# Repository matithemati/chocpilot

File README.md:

# ChocPilot

ChocPilot to przewodowy macropad na własnej płytce ze **STM32F072** i aplikacja na **Windows
i macOS**, w której ustawiasz, co robi każdy element:

- **8 klawiszy Kailh Choc V1** (matryca 2×4) z drukowanymi keycapami,
- kolorowy ekran **[Waveshare 2" IPS LCD 240×320](https://www.tme.eu/pl/details/wsh-17344/wyswietlacze-lcd-graficzne/waveshare/17344/)**
  (ST7789V, SPI; TME WSH-17344) pomiędzy rzędami klawiszy – etykiety albo ikony klawiszy,
  nazwa profilu, nastawy, wygaszacz z animacją i zegarem,
- **2 pokrętła EC11** z przyciskiem i **suwak 45 mm**,
- **12 diod WS2812B** na spodzie (podświetlenie blatu),
- USB-C (USB CDC + HID, bez sterowników).

Firmware jest „cienki”: skanuje klawisze, pokrętła i suwak, rysuje ekran, steruje diodami
i przechowuje kilka ustawień. Całą logikę (gesty, akcje, profile, tryb Klipper) wykonuje
aplikacja. Komunikują się przez USB CDC protokołem JSON Lines ([docs/PROTOCOL.md](docs/PROTOCOL.md)).
Gdy aplikacja nie działa, urządzenie samo wysyła zapisane skróty przez USB HID (tryb awaryjny).

```
firmware/   PlatformIO: chocpilot (STM32F072, STM32duino + TinyUSB), native (testy na PC)
app/        aplikacja Python 3.12+ (PySide6): rdzeń, GUI, symulator, testy, budowanie exe / .app
pcb/        płytka KiCad 10: schemat, PCB, BOM (TME), Gerbery, montaż, mapa pinów
case/       SolidCraft: obudowa, keycapy, gałki, nakładka suwaka, podstawka (STEP / 3MF / STL)
docs/       PROTOCOL.md – protokół urządzenie ↔ aplikacja
```

## Funkcje

- **Gesty**: naciśnięcie, przytrzymanie (próg 500 ms), podwójne naciśnięcie (okno 300 ms).
- **Akcje**: uruchom program (albo przełącz na jego okno; przy kilku oknach kolejne naciśnięcia
  przechodzą między nimi), otwórz plik/folder, adres WWW, skrót klawiszowy (także Win/Cmd,
  F13–F24), wpisz tekst (Unicode), multimedia, głośność systemu i pojedynczego programu
  (Windows), przewijanie, polecenie powłoki, makro, zmiana profilu, warstwa (profil na czas
  trzymania klawisza), tryb Klipper, blokada komputera, wyłączenie ekranu.
- **Profile** z automatycznym przełączaniem według aktywnego programu (np. `obs64.exe` / `OBS`
  → „Stream”), import/eksport do JSON, własny kolor diod dla profilu.
- **Pokrętła i suwak**: każde pokrętło ma akcje dla obrotu w prawo, w lewo i naciśnięcia (te same
  typy akcji co klawisze; głośność i przewijanie mnożą krok przez liczbę zatrzasków). Suwak
  ustawia głośność systemu albo wybranego programu (0–100 %). Domyślnie pokrętło 1 = głośność /
  wycisz, pokrętło 2 = przewijanie / odtwarzaj-pauza.
- **Ekran 320×240**: siatka 2×4 z etykietami albo [ikonami](#ikony-klawiszy) klawiszy, duża
  nazwa profilu, pasek głośności, napis po akcji, znacznik online/offline, tryb testu sprzętu,
  [wygaszacz](#wygaszacz-ekranu) z animacją i godziną. Podgląd w aplikacji rysuje te same piksele.
- **Podświetlenie LED**: stan połączenia, stały kolor, oddychanie, tęcza, wyłączone; błysk diody
  przy naciśniętym klawiszu. Ustawienia zapisane w urządzeniu działają też bez aplikacji.
- **[Tryb Klipper](#tryb-klipper-drukarki-3d)**: sterowanie drukarkami 3D przez Moonraker.
- **Tryb awaryjny HID**: po 3 s bez sygnału z aplikacji klawisze wysyłają skróty wyliczone
  z profilu (akcje „skrót” i „multimedia”), pokrętło 1 zmienia głośność; domyślnie dolny rząd:
  ciszej, głośniej, odtwarzaj/pauza, wycisz.

## Sprzęt

Wszystko o płytce jest w [pcb/README.md](pcb/README.md):

- lista części z numerami TME: [pcb/bom/BOM.md](pcb/bom/BOM.md) (wszystko poza przełącznikami
  Kailh jest w TME, łącznie z ekranem),
- kolejność lutowania i uruchomienie: [pcb/docs/ASSEMBLY.md](pcb/docs/ASSEMBLY.md),
- mapa pinów MCU i złączy: [pcb/docs/PINOUT.md](pcb/docs/PINOUT.md),
- decyzje projektowe, zasilanie, sygnały: [pcb/docs/DESIGN_NOTES.md](pcb/docs/DESIGN_NOTES.md),
- Gerbery do zamówienia płytek: `pcb/fab/gerbers/` (2 warstwy, 1,6 mm – standard JLCPCB / PCBWay).

Obudowa, keycapy, gałki pokręteł, nakładka suwaka i podstawka pod kątem 20°:
[case/README.md](case/README.md) (gotowe pliki STL / 3MF do druku).

Ekran Waveshare 2" przykręca się 4 wkrętami M2 do obudowy i łączy dołączonym kablem PH2.0
ze złączem J2 płytki (1:1, zasilanie 3,3 V).

## Firmware

Wymagania: [PlatformIO](https://platformio.org/) (VS Code + rozszerzenie albo `pip install platformio`).

```bash
cd firmware
pio run
```

- **Rdzeń**: Arduino STM32duino (platforma `ststm32`, płytka `boards/chocpilot.json` = wariant
  generic F072CB), zegar 48 MHz z HSI48 bez kwarcu, dostrajany przez CRS do ramek USB.
- **USB**: [TinyUSB](https://github.com/hathach/tinyusb) 0.18 – urządzenie złożone CDC + HID
  (klawiatura i consumer control), nazwa „ChocPilot”, VID:PID **1209:0001** (pid.codes).
  Aplikacja znajduje port po nazwie, zapasowo po tej parze.
- **Ekran** (`src/display_tft.cpp`, `src/st7789.cpp`): SPI1 12 MHz, tryb 3, bez bufora ramki –
  rysowane są tylko zmienione fragmenty, a po serii komend (np. ikony przy zmianie profilu)
  ekran odświeża się raz, gdy zmiany ustaną. Jasność = PWM podświetlenia, `flip` = obrót o 180°.
  Krój 5×7 ASCII w kilku skalach – polskie litery tracą ogonki (ą → a).
- **Matryca** 2×4 COL2ROW z mapą klawiszy z płytki (`src/boards/board.h`).
- **Pokrętła i suwak** (`src/controls.cpp`): TIM2/TIM3 w trybie enkodera, suwak przez ADC
  z filtrem i histerezą. **Offline** pokrętło 1 zmienia głośność, jego przycisk wycisza.
- **LED** (`src/leds.cpp`, SPI2 3 MHz; efekty `lib/chocpilotcore/src/led_effects.cpp`): jasność
  ograniczona do ok. 1/3 (prąd z USB), przy wygaszaczu wyłączone, w trybie testu kolejno R / G / B / biały.
- **Wygaszacz** (`src/saver.cpp`): animacje z `app/chocpilot/core/savers.py` (jedno źródło dla
  firmware i podglądu) – `python firmware/tools/gen_savers.py` generuje z nich `src/saver_data.h`.
- **Ikony klawiszy** (`src/icons.cpp`): 32×32 px, 16 kolorów, tylko w RAM (aplikacja wysyła je
  po połączeniu).
- **Ustawienia** w emulacji EEPROM rdzenia (ostatnia strona flash) jako blok binarny z CRC
  i numerem wersji – nowsze wersje firmware czytają zapisy starszych.
- **Zużycie** (2026-11, `pio run`): **flash 56 500 B / 128 KB (43 %)**, **RAM 11 228 B / 16 KB (69 %)**.

### Wgrywanie (bootloader DFU w ROM)

Windows:

```powershell
cd firmware
.\flash.ps1
```

Skrypt kompiluje firmware, przełącza działającą płytkę w bootloader (komenda `reboot`) i wgrywa
program przez dfu-util. Opcje: `-BuildOnly` (tylko kompilacja), `-CloseApp` (najpierw zamyka
aplikację ChocPilot, która trzyma port). Bez skryptu (Windows i macOS):

1. Wejście do bootloadera: w aplikacji **Urządzenie → Tryb wgrywania firmware** albo przyciski
   na spodzie płytki (dostęp przez otwory w dnie): trzymaj **BOOT0**, naciśnij i puść **RESET**,
   puść BOOT0. System widzi wtedy „STM32 BOOTLOADER” (0483:DF11).
2. `pio run -t upload` – po wgraniu płytka sama uruchamia program.

Windows za pierwszym razem: przypisz urządzeniu „STM32 BOOTLOADER” sterownik **WinUSB**
programem [Zadig](https://zadig.akeo.ie/) (albo wgraj `.pio\build\chocpilot\firmware.bin` od
adresu 0x08000000 w STM32CubeProgrammer). macOS nie potrzebuje sterownika.

### Testy firmware (na PC)

Parser protokołu, debounce, kody HID, zapis konfiguracji i efekty LED mają testy jednostkowe
w środowisku `native`. Potrzebny jest kompilator gcc/g++ w PATH (Windows: MinGW-w64 –
`pio pkg install -g -t platformio/toolchain-gccmingw32` i dodanie
`%USERPROFILE%\.platformio\packages\toolchain-gccmingw32\bin` do PATH; macOS: Xcode Command Line Tools).

```bash
pio test -e native
```

## Aplikacja

Wymagania: Windows 10/11 albo macOS 12+, Python **3.12+** (sprawdzone na 3.14).

Windows:

```powershell
cd app
python -m venv .venv
.venv\Scripts\python -m pip install -e ".[dev]"
.venv\Scripts\python -m chocpilot
```

macOS:

```bash
cd app
python3 -m venv .venv
.venv/bin/python -m pip install -e ".[dev]"
.venv/bin/python -m chocpilot
```

| Opcja | Działanie |
|---|---|
| `--minimized` | start w zasobniku (macOS: pasek menu) |
| `--config PLIK` | inny plik konfiguracji |
| `--verbose` | dziennik na konsoli |
| `--simulate` | tryb deweloperski: okno symulatora płytki (klawisze, pokrętła, suwak, LED, podgląd LCD) zamiast urządzenia |
| `--version` | wersja aplikacji |

Konfiguracja i dziennik:

| System | Katalog |
|---|---|
| Windows | `%APPDATA%\ChocPilot` |
| macOS | `~/Library/Application Support/ChocPilot` |

`config.json` (zapis atomowy, poprzednia wersja w `config.json.bak`), `chocpilot.log`
(rotacja 3 × 512 KB), `icons/` (własne ikony). Uszkodzony plik konfiguracji jest odkładany
jako `config.broken.json`, a aplikacja wczytuje kopię zapasową. Nieobsłużone błędy trafiają do
dziennika z pełnym śladem i pokazują jedno okno z informacją – aplikacja działa dalej.

Obsługa:

- Lista profili po lewej (dwuklik = aktywuj). Kliknij klawisz, pokrętło albo suwak na podglądzie,
  aby edytować; przyciski **Testuj** wykonują akcję od razu. Fizyczne naciśnięcia podświetlają
  elementy podglądu.
- **Plik → Ustawienia**: port (auto/ręczny), jasność, wygaszacz i jego animacja, tryb ekranu,
  obrót, podświetlenie LED (podgląd na żywo), progi gestów, debounce, skróty trybu awaryjnego,
  autostart, start zminimalizowany, motyw, język (PL/EN).
- Zamknięcie okna chowa aplikację do zasobnika (kolor ikony = stan połączenia). Z zasobnika:
  zmiana profilu, **Wstrzymaj akcje**, wyjście. Uruchamia się tylko jedna instancja.

### macOS – uprawnienia i ograniczenia

- **Dostępność** (Ustawienia systemowe → Prywatność i ochrona → Dostępność): wymagana do skrótów,
  wpisywania tekstu, przewijania, blokady ekranu i przełączania okien. Przy pierwszym starcie
  macOS sam pokazuje prośbę, a aplikacja wyjaśnia, co włączyć; po włączeniu uruchom ją ponownie.
- **Automatyzacja**: przy pierwszym poleceniu powłoki uruchamianym w widocznym oknie macOS pyta
  o zgodę na sterowanie Terminalem (AppleScript) – zezwól.
- Głośność **pojedynczego programu** nie jest dostępna (macOS nie ma do tego publicznego API);
  głośność systemu działa.
- Autostart = LaunchAgent `~/Library/LaunchAgents/com.chocpilot.app.plist` (włączany w Ustawieniach).

### Testy i jakość

```bash
cd app
.venv/Scripts/python -m pytest          # macOS: .venv/bin/python
.venv/Scripts/python -m ruff check chocpilot tests
.venv/Scripts/python -m ruff format --check chocpilot tests
.venv/Scripts/python -m mypy chocpilot
```

Testy nie wymagają urządzenia (atrapy portu szeregowego, platformy i symulator). Testy GUI
działają w trybie `offscreen` (pytest-qt).

### Budowanie – Windows (ChocPilot.exe)

```powershell
cd app
.\build_exe.ps1
```

Skrypt instaluje zależności, generuje ikony (`scripts/make_icon.py`) i uruchamia PyInstaller
(`chocpilot.spec`): jeden plik bez konsoli, z ikoną i metadanymi wersji (Właściwości pliku).
Wynik: `app\dist\ChocPilot.exe`. Działającą kopię z `dist` skrypt zamyka przed budowaniem
i uruchamia ponownie (`-NoRestart` – bez ponownego uruchomienia).

### Budowanie – macOS (ChocPilot.app)

```bash
cd app
./build_macos.sh
```

Skrypt (na Macu, z Pythonem 3.12+ z python.org albo Homebrew i Xcode Command Line Tools)
tworzy `.venv`, uruchamia testy, generuje ikonę `.icns`, buduje **`dist/ChocPilot.app`**
(PyInstaller, architektura Pythona – na Apple Silicon `arm64`), podpisuje ją ad-hoc i pakuje
do **`dist/ChocPilot-<wersja>-macOS-<arch>.dmg`** (przeciągnij do Aplikacji). Opcje:
`--skip-tests`, `--no-dmg`.

- Pierwsze uruchomienie aplikacji podpisanej ad-hoc: Finder → prawy klik → **Otwórz** (albo
  `xattr -dr com.apple.quarantine /Applications/ChocPilot.app`), bo Gatekeeper nie zna autora.
- Do dystrybucji innym osobom: `CODESIGN_IDENTITY="Developer ID Application: …" ./build_macos.sh`
  podpisuje certyfikatem Apple (hardened runtime); potem notaryzacja:
  `xcrun notarytool submit dist/ChocPilot-*.dmg --keychain-profile <profil> --wait`
  i `xcrun stapler staple dist/ChocPilot-*.dmg`.
- Po każdej przebudowie podpisanej ad-hoc macOS może zapomnieć uprawnienie Dostępność – wyłącz
  i włącz ChocPilot na liście (albo usuń i dodaj ponownie).

### Wersje

Jedno źródło wersji aplikacji: `app/chocpilot/__init__.py` (`__version__`) – używają go pakiet
Pythona, okno „O programie”, metadane exe i `Info.plist`. Wersja firmware: `CHOCPILOT_FW_VERSION`
w `firmware/platformio.ini`; aplikacja pokazuje ją na pasku stanu.

### Architektura aplikacji

```
chocpilot/core/protocol.py    kodowanie/dekodowanie JSON Lines, walidacja, transliteracja (krój ASCII)
chocpilot/core/transport.py   interfejs + port szeregowy (wątek, wykrywanie, ponowne łączenie)
chocpilot/core/simulator.py   symulator urządzenia (ta sama logika co firmware) + transport w procesie
chocpilot/core/gestures.py    tap / hold / double_tap (czysta logika, czas z zewnątrz)
chocpilot/core/actions/       rejestr typów akcji, wbudowane akcje, wykonawca (pula wątków)
chocpilot/core/config.py      modele pydantic, migracje schema_version, zapis atomowy, import/eksport
chocpilot/core/profiles.py    aktywny profil, warstwy, automatyczne przełączanie
chocpilot/core/engine.py      kontroler: zdarzenia → gesty → akcje; profil → ekran, ikony, LED, skróty HID
chocpilot/core/klipper.py     tryb Klipper (moonraker.py – klient HTTP Moonrakera)
chocpilot/core/leds.py        efekty LED (jak firmware – podgląd), savers.py – animacje wygaszacza
chocpilot/platform/           kod zależny od systemu: windows.py, macos.py (base.py = interfejs)
chocpilot/gui/                PySide6: okno główne, edytory, ustawienia, zasobnik, symulator
chocpilot/gui/lcd.py          podgląd ekranu LCD 320×240 – ten sam krój i układ co firmware
chocpilot/gui/icon_*.py       biblioteka i wybór ikon klawiszy
```

Nowy typ akcji: klasa dziedzicząca po `ActionBase` z polem `type: Literal["nazwa"]`, metodą
`run(ctx)` i dekoratorem `@register_action("nazwa", "Etykieta")`. Formularz w GUI tworzy się
automatycznie z pól modelu.

## Ikony klawiszy

Każdy klawisz może mieć na ekranie ikonę zamiast etykiety: edytor klawisza → **Ikona na
ekranie** → *Wybierz ikonę…*. Okno wyboru ma wyszukiwarkę i kategorie:

- **wbudowane** – ok. 120 ikon liniowych (multimedia, edycja, programy, system, streaming, druk 3D,
  symbole), zdefiniowane w `app/chocpilot/gui/icon_set.py`; nowa ikona = jeden wiersz SVG,
- **emoji** – wszystkie emoji czcionki systemu (Windows: Segoe UI Emoji, macOS: Apple Color
  Emoji), wyszukiwane po angielskiej nazwie Unicode,
- **własne** – pliki PNG / SVG / JPG z folderu `icons` w katalogu konfiguracji (przycisk *Folder
  własnych ikon*, potem *Odśwież*).

Aplikacja zamienia ikonę na 32 × 32 px w 16 kolorach na tle kafelka i wysyła ją do urządzenia
(komenda `icon`), które rysuje ją w skali 2. Przy zmianie profilu ikony idą przed siatką, więc
nowy ekran pojawia się od razu z kompletem ikon. Etykieta zostaje – pokazuje się w podglądzie
po naciśnięciu i po restarcie płytki bez aplikacji.

## Wygaszacz ekranu

Po czasie `screensaver_s` (Ustawienia → Urządzenie) ekran gaśnie albo pokazuje animację –
po trawie skacze królik albo kłusuje corgi, a u góry na środku jest godzina HH:MM (czas podaje
aplikacja, płytka liczy dalej sama). Wybór: **Ustawienia → Urządzenie → Animacja wygaszacza**.
Dowolny klawisz / pokrętło budzi ekran, diody LED w tym czasie są zgaszone. Nowa animacja =
wpis w `SAVERS` (`app/chocpilot/core/savers.py`, ramki jako tekst) + `firmware/tools/gen_savers.py`.

## Tryb Klipper (drukarki 3D)

ChocPilot może sterować drukarkami 3D z [Klipperem](https://www.klipper3d.org/) przez API
[Moonrakera](https://moonraker.readthedocs.io/) (to samo, którego używają Mainsail i Fluidd).
Konfiguracja: strona **Klipper** w aplikacji.

- **Drukarki:** nazwa, adres Moonrakera (np. `http://voron.local` albo `192.168.1.20:7125`),
  opcjonalny klucz API; przycisk *Testuj połączenie* pokazuje stan drukarki.
- **Włączanie trybu:** przytrzymaj przycisk pokrętła E2 (domyślnie 0,8 s; do wyboru E1 albo tylko
  akcja). Krótkie naciśnięcie tego pokrętła działa jak zwykle (wykonuje się po puszczeniu).
  Akcję **Tryb Klipper** (włącz / wyłącz / przełącz) można też przypisać do dowolnego klawisza.
- **W trybie Klipper:**
  - klawisze K1–K8 – polecenia z ustawień (każde z ikoną): G-code / makro, pauza / wznowienie,
    anuluj wydruk, awaryjne zatrzymanie, restart firmware, następna drukarka, wyjście. Domyślnie:
    Home, Pauza, PLA (stół 60 °C, dysza 200 °C), Stygnij, Silniki, Anuluj (przytrzymanie),
    Drukarka, STOP (przytrzymanie);
  - pokrętło E1 – ruch osi (naciśnięcie: X → Y → Z, krok i prędkość w ustawieniach; wymaga
    bazowania osi); w trakcie wydruku – Z offset w locie (`SET_GCODE_OFFSET Z_ADJUST`);
  - pokrętło E2 – temperatura dyszy / stołu, prędkość (M220), przepływ (M221), wentylator;
    naciśnięcie zmienia parametr;
  - suwak – wentylator chłodzenia albo prędkość wydruku 50–150 %;
  - ekran – w tytule nazwa drukarki, stan (postęp wydruku) i temperatury, w siatce ikony
    poleceń; nastawy pokazują się na chwilę na ekranie.
- Szybkie kręcenie pokrętłem wysyła tylko najnowszą nastawę (bez kolejki starych poleceń).
  Klucz API jest zapisywany w pliku konfiguracji aplikacji.

## Rozwiązywanie problemów

| Objaw | Co sprawdzić |
|---|---|
| Aplikacja „szuka ChocPilot…” | Kabel z transmisją danych (nie tylko ładowanie). Zamknij monitor portu PlatformIO (port może być zajęty). W Ustawieniach wybierz port ręcznie (Windows: `COMx`, macOS: `/dev/cu.usbmodem…`). Dziennik pokazuje próby. |
| Płytka nie pojawia się w systemie | Sprawdź **+5V** i **+3V3** (pcb/docs/ASSEMBLY.md, test 1) i lut USB-C. Płytka bez firmware zgłasza się tylko jako „STM32 BOOTLOADER” – wgraj firmware. |
| `flash.ps1` / `pio run -t upload`: brak urządzenia DFU | Windows: sterownik WinUSB dla „STM32 BOOTLOADER” (Zadig). Wejdź do bootloadera ręcznie: BOOT0 + RESET. |
| Pusty / biały ekran | Kabel PH2.0 do J2 (VCC na pin 1, kolejność 1:1), lut J2. W trybie testu (K1 + K4 przez 3 s po podłączeniu) ekran pokazuje stan klawiszy. |
| Obraz do góry nogami | Ustawienia → Urządzenie → **Obróć ekran o 180°**. |
| Polskie litery bez ogonków | To nie błąd: krój ekranu ma tylko ASCII. |
| Kilka klawiszy reaguje naraz | Odwrócona dioda albo brak diody; sprawdź w trybie testu sprzętu. |
| Klawisz „drga” | Zwiększ debounce (Ustawienia → Urządzenie). |
| Pokrętło działa odwrotnie | Kierunek w firmware: `kEncoderDir` w `firmware/src/boards/board.h`. |
| Przełączanie na okno programu nie działa | Windows czasem blokuje przejęcie fokusu (program i tak jest uruchamiany, gdy nie ma okna); macOS – uprawnienie Dostępność. |
| Skróty i tekst nic nie robią (macOS) | Uprawnienie **Dostępność** dla ChocPilot (po przebudowie aplikacji wyłącz i włącz je ponownie). |
| Głośność programu „nie gra” | Windows: program musi mieć aktywną sesję audio (widoczną w mikserze głośności). macOS: funkcja niedostępna. |
| SmartScreen / antywirus ostrzega o ChocPilot.exe | Plik nie jest podpisany; pynput (symulacja klawiatury) bywa oznaczany heurystycznie. Można uruchamiać z Pythona. |
| Akcje wykonują się podwójnie | Nie powinno: gdy aplikacja jest połączona, HID urządzenia jest wyłączony. Sprawdź, czy nie działają dwie kopie aplikacji (np. zbudowana i z Pythona). |
| Coś innego | Zakładka **Dziennik** w aplikacji albo `chocpilot.log` w katalogu konfiguracji. |

## Licencja

MIT.

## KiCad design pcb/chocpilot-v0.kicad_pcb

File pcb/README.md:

# ChocPilot – płytka (KiCad 10)

Sprzęt ChocPilot (rewizja płytki **v0** – nazwa plików KiCad): 8 klawiszy Kailh Choc V1 lutowanych w płytkę (2 rzędy po 4, matryca
z diodą przy każdym klawiszu),
kolorowy ekran [Waveshare 2" IPS LCD 240×320](https://www.tme.eu/pl/details/wsh-17344/wyswietlacze-lcd-graficzne/waveshare/17344/)
(TME WSH-17344, ST7789V, SPI; przykręcony do obudowy) pomiędzy nimi, 2 enkodery EC11 po lewej, suwak 45 mm po prawej,
12 diod WS2812B na spodzie (podświetlenie blatu) i własny mikrokontroler STM32F072 z USB-C.
Płytka 114 × 93 mm, 2 warstwy, wszystko poza elementami istniejącymi tylko w THT – SMD
w obudowach do ręcznego lutowania (0805, SOT-23, LQFP-48).

| Plik | Zawartość |
|---|---|
| `chocpilot-v0.kicad_pro/.kicad_sch/.kicad_pcb` | projekt KiCad 10 (schemat A3, płytka z trasami i wylewkami GND) |
| `chocpilot.pretty/` | footprinty własne: Kailh Choc V1/V2 (THT), suwak ALPS RS45111 |
| [bom/BOM.md](bom/BOM.md), [bom/chocpilot-v0-bom.csv](bom/chocpilot-v0-bom.csv) | lista części z numerami TME / Amazon |
| [docs/PINOUT.md](docs/PINOUT.md) | mapa pinów MCU, złącza, kolejność LED |
| [docs/ASSEMBLY.md](docs/ASSEMBLY.md) | kolejność lutowania i uruchomienie |
| [docs/DESIGN_NOTES.md](docs/DESIGN_NOTES.md) | decyzje projektowe, zasilanie, sygnały, rzeczy do sprawdzenia przed zamówieniem |
| `img/` | podgląd: `schematic.pdf/.png`, `pcb_top/bottom.png` (warstwy), `render_top/bottom.png` (3D) |
| `fab/gerbers/` | Gerbery + wiercenia (Excellon) do zamówienia płytek – spakuj zawartość do ZIP albo `tools/export_fab.sh` |
| `production/` | pliki montażu SMT (BOM, pozycje elementów, netlista IPC) z wtyczki Fabrication Toolkit |
| `tools/` | generatory – patrz niżej |

## Dlaczego STM32F072CBT6, a nie RP2040

- **Obudowa.** RP2040 istnieje tylko jako QFN-56 0,4 mm z padem termicznym pod spodem – bez
  gorącego powietrza / pieca praktycznie nie do przylutowania kolbą. STM32F072CBT6 to
  **LQFP-48 0,5 mm z wyprowadzeniami na zewnątrz**: lutuje się zwykłą kolbą metodą „drag”
  z topnikiem, a mostki widać i łatwo zebrać plecionką.
- **Mniej części.** F072 ma USB FS **bez kwarcu** (HSI48 synchronizowany przez CRS z ramkami
  USB), pamięć programu w środku (128 KB) i **bootloader USB DFU w ROM** (BOOT0 + RESET).
  RP2040 wymaga zewnętrznego flasha QSPI (SOIC-8 lub USON), kwarcu 12 MHz i dodatkowego
  odsprzęgania wewnętrznego regulatora 1,1 V.
- **Wystarczająca wydajność.** F072 ma 128 KB flash / 16 KB RAM (firmware zajmuje ok. 43 % /
  69 %), sprzętowe SPI, ADC 12-bit, timery z trybem enkodera (TIM2, TIM3) i SPI do sterowania
  WS2812.
- **Dostępność.** STM32F072CBT6 jest w TME, wspierany przez STM32duino (PlatformIO `ststm32`)
  i QMK.

Kwarc 8 MHz (Y1) jest na płytce jako **opcja** – USB go nie potrzebuje; daje dokładniejszy zegar,
jeśli kiedyś będzie potrzebny (można nie lutować Y1, C13, C14).

## Weryfikacja (KiCad 10.0.7, `kicad-cli`)

- **ERC:** 0 błędów, 0 ostrzeżeń.
- **DRC** (`--severity-all --schematic-parity`, także z `--refill-zones`): 0 naruszeń,
  0 niepołączonych, 0 rozbieżności ze schematem.
- Reguły: odstęp miedź–miedź 0,2 mm, ścieżki 0,25 mm (sygnały) / 0,3 mm (+3V3, GND) /
  0,6 mm (VBUS, +5V), przelotki 0,6/0,3 mm, krawędź 0,3 mm (trasowane z 0,5 mm), otwór–miedź
  0,15 mm (kołki ustalające USB-C mają 0,19 mm do padów GND w bibliotecznym footprincie).
  Mieści się w standardzie tanich fabryk (JLCPCB, PCBWay: 2 warstwy, 1,6 mm, 1 oz).

Do zrobienia przed zamówieniem płytek – patrz [DESIGN_NOTES.md](docs/DESIGN_NOTES.md#do-sprawdzenia-przed-zamowieniem):
wydruk 1:1 i przymiarka footprintu Choc, mocowanie ekranu LCD w obudowie i długość jego kabla do J2, przymiarka footprintu suwaka ALPS.

## Generowanie

Schemat, płytka i BOM powstają ze skryptów w `tools/` (dane: [`tools/design.py`](tools/design.py)).
Ręczne poprawki w KiCad są możliwe, ale kolejne generowanie je nadpisze – zmieniaj `design.py`.

```bash
cd pcb
python3 tools/gen_pro.py        # reguły DRC i klasy sieci
python3 tools/gen_sch.py        # schemat
/Applications/KiCad/KiCad.app/Contents/Frameworks/Python.framework/Versions/Current/bin/python3 tools/gen_pcb.py
python3 tools/gen_bom.py        # BOM.md + CSV
tools/render.sh img             # podgląd PNG
tools/export_fab.sh             # Gerbery
```

Windows (KiCad 10 w `C:\Program Files\KiCad\10.0`, inna ścieżka – zmienna `KICAD_ROOT`;
ścieżki instalacji są w [`tools/kicad_env.py`](tools/kicad_env.py)):

```bash
python tools/gen_sch.py
"/c/Program Files/KiCad/10.0/bin/python.exe" tools/gen_pcb.py
python tools/gen_bom.py
```

`gen_pcb.py` używa Pythona dołączonego do KiCad (moduł `pcbnew`), eksportuje netlistę ze
schematu przez `kicad-cli` i trasuje płytkę własnym routerem [`tools/router.py`](tools/router.py)
(A* na siatce 0,25 mm, 2 warstwy; ok. 1 min). `--reuse` używa zapisanych tras z
`tools/build/`. Na macOS `kicad-cli` uruchamiany z piaskownicy potrafi zawisnąć przy starcie –
wtedy trzeba go uruchomić poza nią.

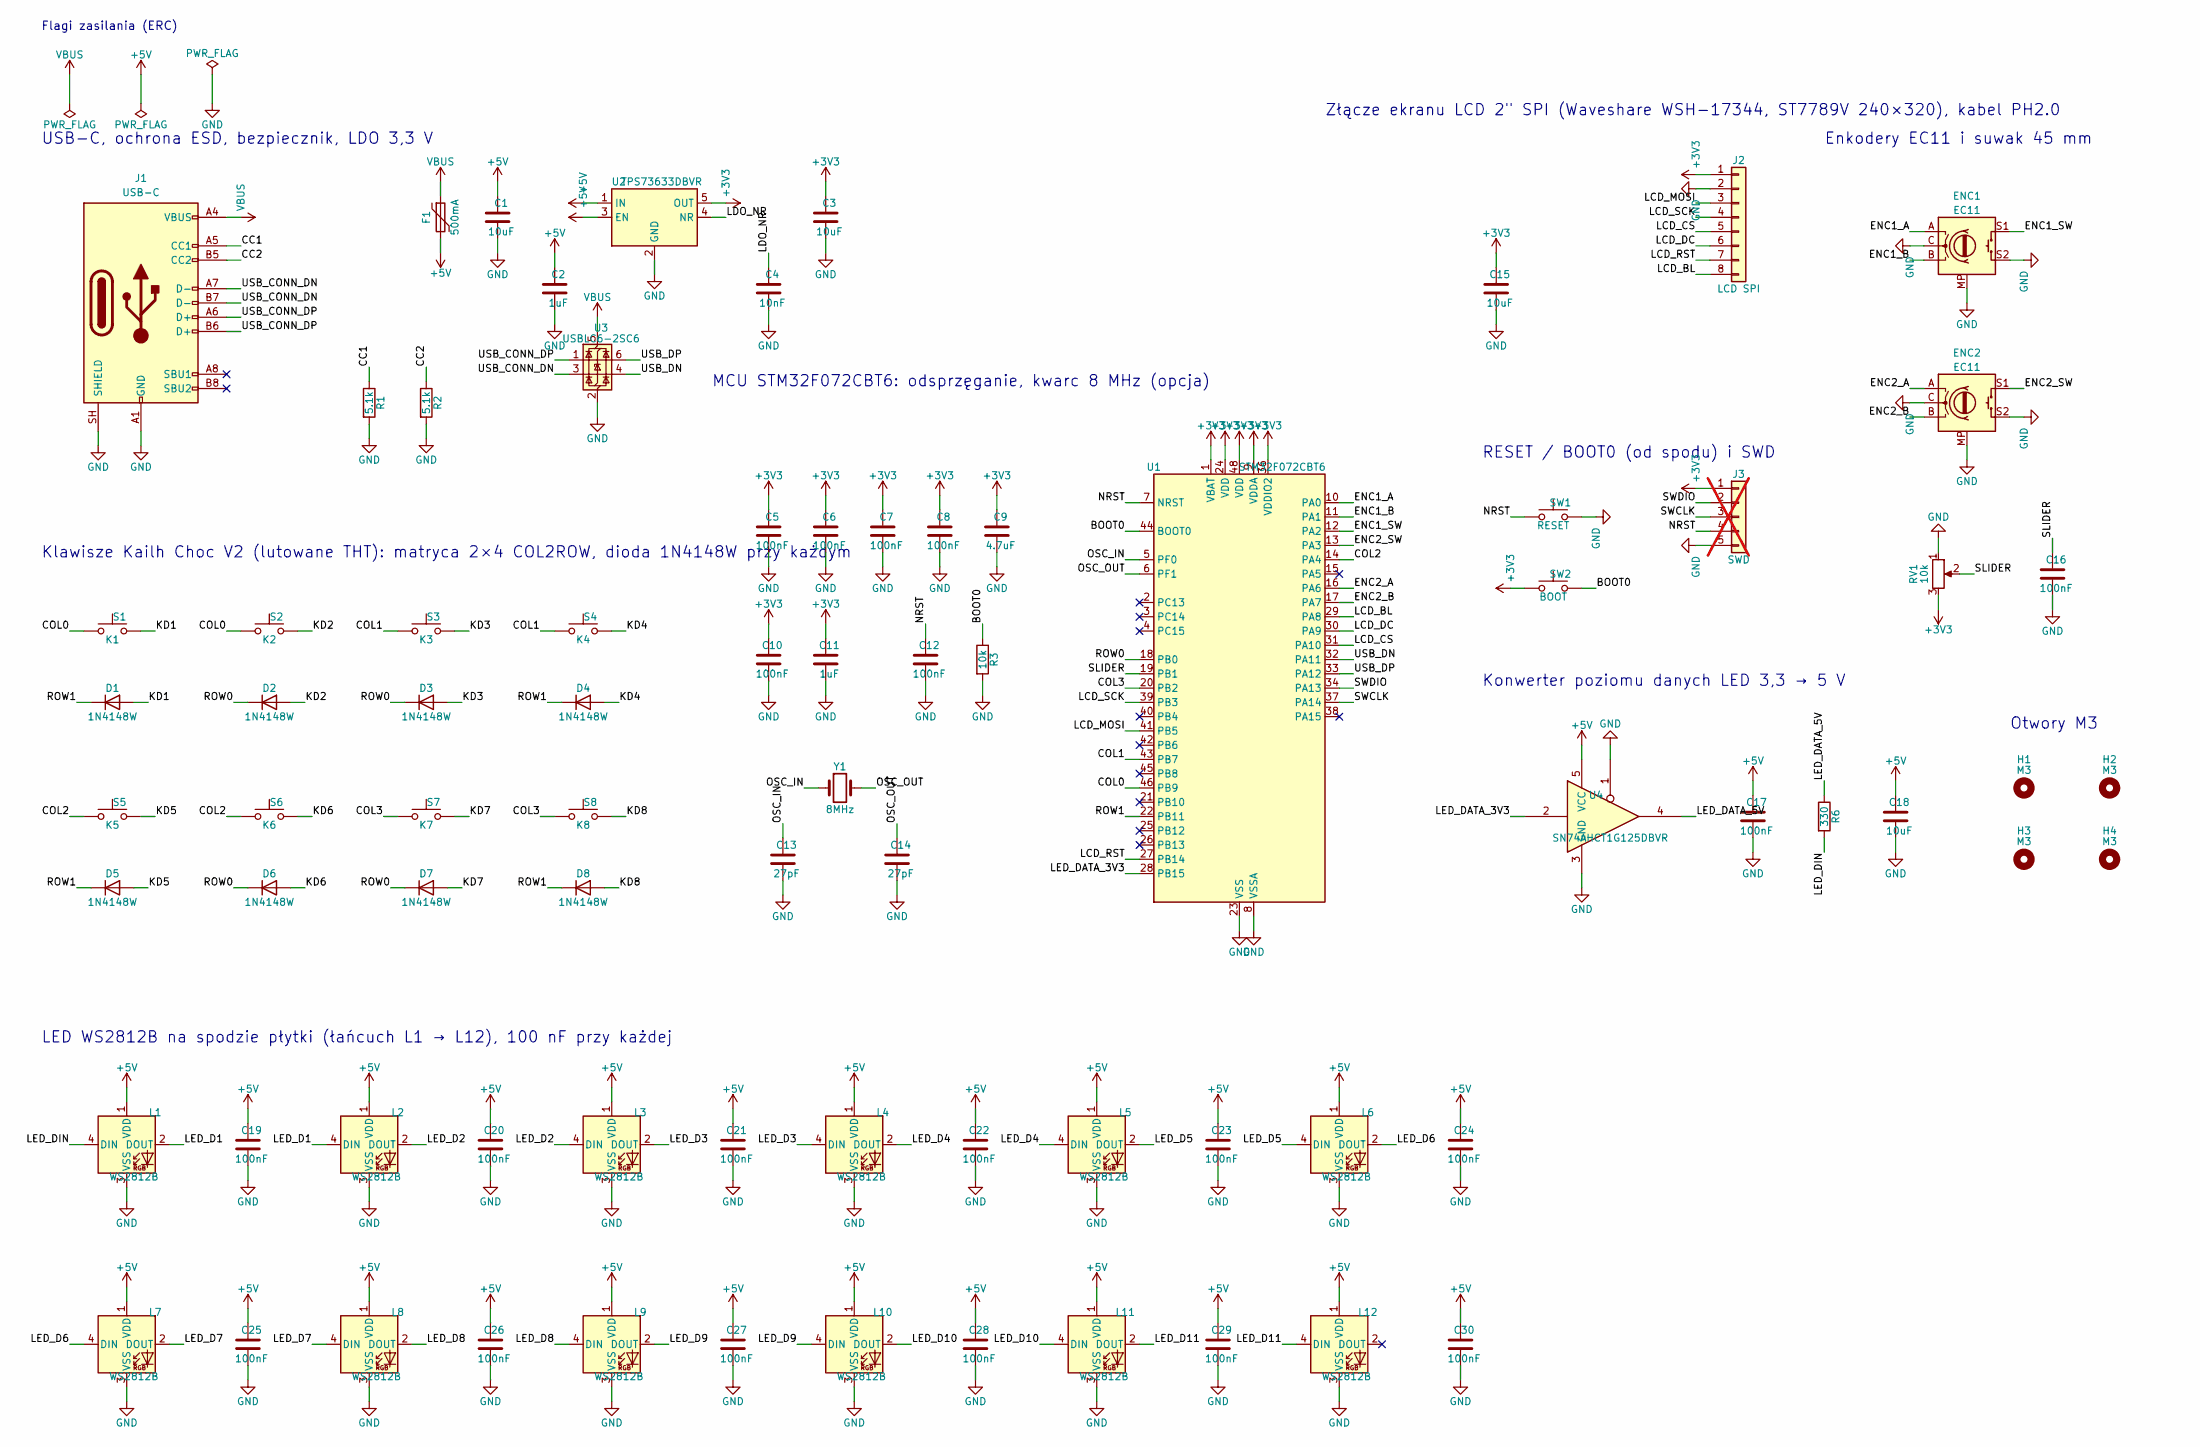
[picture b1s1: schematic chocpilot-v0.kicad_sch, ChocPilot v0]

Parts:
C1, C3, C15, C18: 10uF; C_0805_2012Metric_Pad1.18x1.45mm_HandSolder; MPN C0805C106M8RACTU
C2, C11: 1uF; C_0805_2012Metric_Pad1.18x1.45mm_HandSolder; MPN KAM21KR71E105KU
C4: 10nF; C_0805_2012Metric_Pad1.18x1.45mm_HandSolder; MPN KGM21NR72A103KT
C5, C6, C7, C8, C10, C12, C16, C17, C19, C20, C21, C22, C23, C24, C25, C26, C27, C28, C29, C30: 100nF; C_0805_2012Metric_Pad1.18x1.45mm_HandSolder; MPN KAM21BR71H104KT
C9: 4.7uF; C_0805_2012Metric_Pad1.18x1.45mm_HandSolder; MPN KGM21AR71C475KU
C13, C14: 27pF; C_0805_2012Metric_Pad1.18x1.45mm_HandSolder; MPN 08055A270GAT2A
D1, D2, D3, D4, D5, D6, D7, D8: 1N4148W; D_SOD-123; MPN 1N4148W-E3-08
ENC1, ENC2: EC11; RotaryEncoder_Alps_EC11E-Switch_Vertical_H20mm; MPN EC11E15244G1
F1: 500mA; Fuse_1206_3216Metric_Pad1.42x1.75mm_HandSolder; MPN MF-NSMF050-2
H1, H2, H3, H4: M3; MountingHole_3.2mm_M3
J1: USB-C; USB_C_Receptacle_GCT_USB4105-xx-A_16P_TopMnt_Horizontal; MPN USB4105-GF-A
J2: LCD SPI; PinHeader_1x08_P2.54mm_Vertical; MPN DS1021-1*8SF11-B
J3: SWD; PinHeader_1x05_P2.54mm_Vertical; MPN DS1021-1*5SF11-B; not fitted
L1, L2, L3, L4, L5, L6, L7, L8, L9, L10, L11, L12: WS2812B; LED_WS2812B_PLCC4_5.0x5.0mm_P3.2mm; MPN WS2812B-V6
R1, R2: 5.1k; R_0805_2012Metric_Pad1.20x1.40mm_HandSolder; MPN RC0805FR-075K1L
R3: 10k; R_0805_2012Metric_Pad1.20x1.40mm_HandSolder; MPN RC0805FR-0710KL
R6: 330; R_0805_2012Metric_Pad1.20x1.40mm_HandSolder; MPN RC0805FR-07330RL
RV1: 10k; Potentiometer_Alps_RS45111_Slide_45mm; MPN RS45111A900F
S1: K1; SW_Kailh_Choc_V1V2_1u; MPN CPG1353 (Choc V2)
S2: K2; SW_Kailh_Choc_V1V2_1u; MPN CPG1353 (Choc V2)
S3: K3; SW_Kailh_Choc_V1V2_1u; MPN CPG1353 (Choc V2)
S4: K4; SW_Kailh_Choc_V1V2_1u; MPN CPG1353 (Choc V2)
S5: K5; SW_Kailh_Choc_V1V2_1u; MPN CPG1353 (Choc V2)
S6: K6; SW_Kailh_Choc_V1V2_1u; MPN CPG1353 (Choc V2)
S7: K7; SW_Kailh_Choc_V1V2_1u; MPN CPG1353 (Choc V2)
S8: K8; SW_Kailh_Choc_V1V2_1u; MPN CPG1353 (Choc V2)
SW1: RESET; SW_SPST_PTS645Sx43SMTR92; MPN PTS645SM43SMTR92 LFS
SW2: BOOT; SW_SPST_PTS645Sx43SMTR92; MPN PTS645SM43SMTR92 LFS
U1: STM32F072CBT6; LQFP-48_7x7mm_P0.5mm; MPN STM32F072CBT6
U2: TPS73633DBVR; SOT-23-5_HandSoldering; MPN TPS73633DBVR
U3: USBLC6-2SC6; SOT-23-6_Handsoldering; MPN USBLC6-2SC6
U4: SN74AHCT1G125DBVR; SOT-23-5_HandSoldering; MPN SN74AHCT1G125DBVR
Y1: 8MHz; Crystal_SMD_5032-2Pin_5.0x3.2mm_HandSoldering; MPN ABM3-8.000MHZ-D2Y-T

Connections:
+3V3: C3.1, C5.1, C6.1, C7.1, C8.1, C9.1, C10.1, C11.1, C15.1, J2.1, J3.1, RV1.3, SW2.1, U1.1 (VBAT), U1.9 (VDDA), U1.24 (VDD), U1.36 (VDDIO2), U1.48 (VDD), U2.5 (OUT)
+5V: C1.1, C2.1, C17.1, C18.1, C19.1, C20.1, C21.1, C22.1, C23.1, C24.1, C25.1, C26.1, C27.1, C28.1, C29.1, C30.1, F1.2, L1.1 (VDD), L2.1 (VDD), L3.1 (VDD), L4.1 (VDD), L5.1 (VDD), L6.1 (VDD), L7.1 (VDD), L8.1 (VDD), L9.1 (VDD), L10.1 (VDD), L11.1 (VDD), L12.1 (VDD), U2.1 (IN), U2.3 (EN), U4.5 (VCC)
/BOOT0: R3.1, SW2.2, U1.44 (BOOT0)
/CC1: J1.A5 (CC1), R1.1
/CC2: J1.B5 (CC2), R2.1
/COL0: S1.1, S2.1, U1.46 (PB9)
/COL1: S3.1, S4.1, U1.43 (PB7)
/COL2: S5.1, S6.1, U1.14 (PA4)
/COL3: S7.1, S8.1, U1.20 (PB2)
/ENC1_A: ENC1.A, U1.10 (PA0)
/ENC1_B: ENC1.B, U1.11 (PA1)
/ENC1_SW: ENC1.S1, U1.12 (PA2)
/ENC2_A: ENC2.A, U1.16 (PA6)
/ENC2_B: ENC2.B, U1.17 (PA7)
/ENC2_SW: ENC2.S1, U1.13 (PA3)
/KD1: D1.2 (A), S1.2
/KD2: D2.2 (A), S2.2
/KD3: D3.2 (A), S3.2
/KD4: D4.2 (A), S4.2
/KD5: D5.2 (A), S5.2
/KD6: D6.2 (A), S6.2
/KD7: D7.2 (A), S7.2
/KD8: D8.2 (A), S8.2
/LCD_BL: J2.8, U1.29 (PA8)
/LCD_CS: J2.5, U1.31 (PA10)
/LCD_DC: J2.6, U1.30 (PA9)
/LCD_MOSI: J2.3, U1.41 (PB5)
/LCD_RST: J2.7, U1.27 (PB14)
/LCD_SCK: J2.4, U1.39 (PB3)
/LDO_NR: C4.1, U2.4 (NR)
/LED_D1: L1.2 (DOUT), L2.4 (DIN)
/LED_D2: L2.2 (DOUT), L3.4 (DIN)
/LED_D3: L3.2 (DOUT), L4.4 (DIN)
/LED_D4: L4.2 (DOUT), L5.4 (DIN)
/LED_D5: L5.2 (DOUT), L6.4 (DIN)
/LED_D6: L6.2 (DOUT), L7.4 (DIN)
/LED_D7: L7.2 (DOUT), L8.4 (DIN)
/LED_D8: L8.2 (DOUT), L9.4 (DIN)
/LED_D9: L9.2 (DOUT), L10.4 (DIN)
/LED_D10: L10.2 (DOUT), L11.4 (DIN)
/LED_D11: L11.2 (DOUT), L12.4 (DIN)
/LED_DATA_3V3: U1.28 (PB15), U4.2
/LED_DATA_5V: R6.1, U4.4
/LED_DIN: L1.4 (DIN), R6.2
/NRST: C12.1, J3.4, SW1.1, U1.7 (NRST)
/OSC_IN: C13.1, U1.5 (PF0), Y1.1
/OSC_OUT: C14.1, U1.6 (PF1), Y1.2
/ROW0: D2.1 (K), D3.1 (K), D6.1 (K), D7.1 (K), U1.18 (PB0)
/ROW1: D1.1 (K), D4.1 (K), D5.1 (K), D8.1 (K), U1.22 (PB11)
/SLIDER: C16.1, RV1.2, U1.19 (PB1)
/SWCLK: J3.3, U1.37 (PA14)
/SWDIO: J3.2, U1.34 (PA13)
/USB_CONN_DN: J1.A7 (D-), J1.B7 (D-), U3.3 (I/O2)
/USB_CONN_DP: J1.A6 (D+), J1.B6 (D+), U3.1 (I/O1)
/USB_DN: U1.32 (PA11), U3.4 (I/O2)
/USB_DP: U1.33 (PA12), U3.6 (I/O1)
GND: C1.2, C2.2, C3.2, C4.2, C5.2, C6.2, C7.2, C8.2, C9.2, C10.2, C11.2, C12.2, C13.2, C14.2, C15.2, C16.2, C17.2, C18.2, C19.2, C20.2, C21.2, C22.2, C23.2, C24.2, C25.2, C26.2, C27.2, C28.2, C29.2, C30.2, ENC1.C, ENC1.MP, ENC1.S2, ENC2.C, ENC2.MP, ENC2.S2, J1.A1 (GND), J1.A12 (GND), J1.B1 (GND), J1.B12 (GND), J1.SH (SHIELD), J2.2, J3.5, L1.3 (VSS), L2.3 (VSS), L3.3 (VSS), L4.3 (VSS), L5.3 (VSS), L6.3 (VSS), L7.3 (VSS), L8.3 (VSS), L9.3 (VSS), L10.3 (VSS), L11.3 (VSS), L12.3 (VSS), R1.2, R2.2, R3.2, RV1.1, SW1.2, U1.8 (VSSA), U1.23 (VSS), U1.35 (VSS), U1.47 (VSS), U2.2 (GND), U3.2 (GND), U4.1, U4.3 (GND)
VBUS: F1.1, J1.A4 (VBUS), J1.A9 (VBUS), J1.B4 (VBUS), J1.B9 (VBUS), U3.5 (VBUS)

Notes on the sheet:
USB-C, ochrona ESD, bezpiecznik, LDO 3,3 V
MCU STM32F072CBT6: odsprzęganie, kwarc 8 MHz (opcja)
Złącze ekranu LCD 2" SPI (Waveshare WSH-17344, ST7789V 240×320), kabel PH2.0
Enkodery EC11 i suwak 45 mm
Klawisze Kailh Choc V2 (lutowane THT): matryca 2×4 COL2ROW, dioda 1N4148W przy każdym
RESET / BOOT0 (od spodu) i SWD
Konwerter poziomu danych LED 3,3 → 5 V
LED WS2812B na spodzie płytki (łańcuch L1 → L12), 100 nF przy każdej
Otwory M3
Flagi zasilania (ERC)

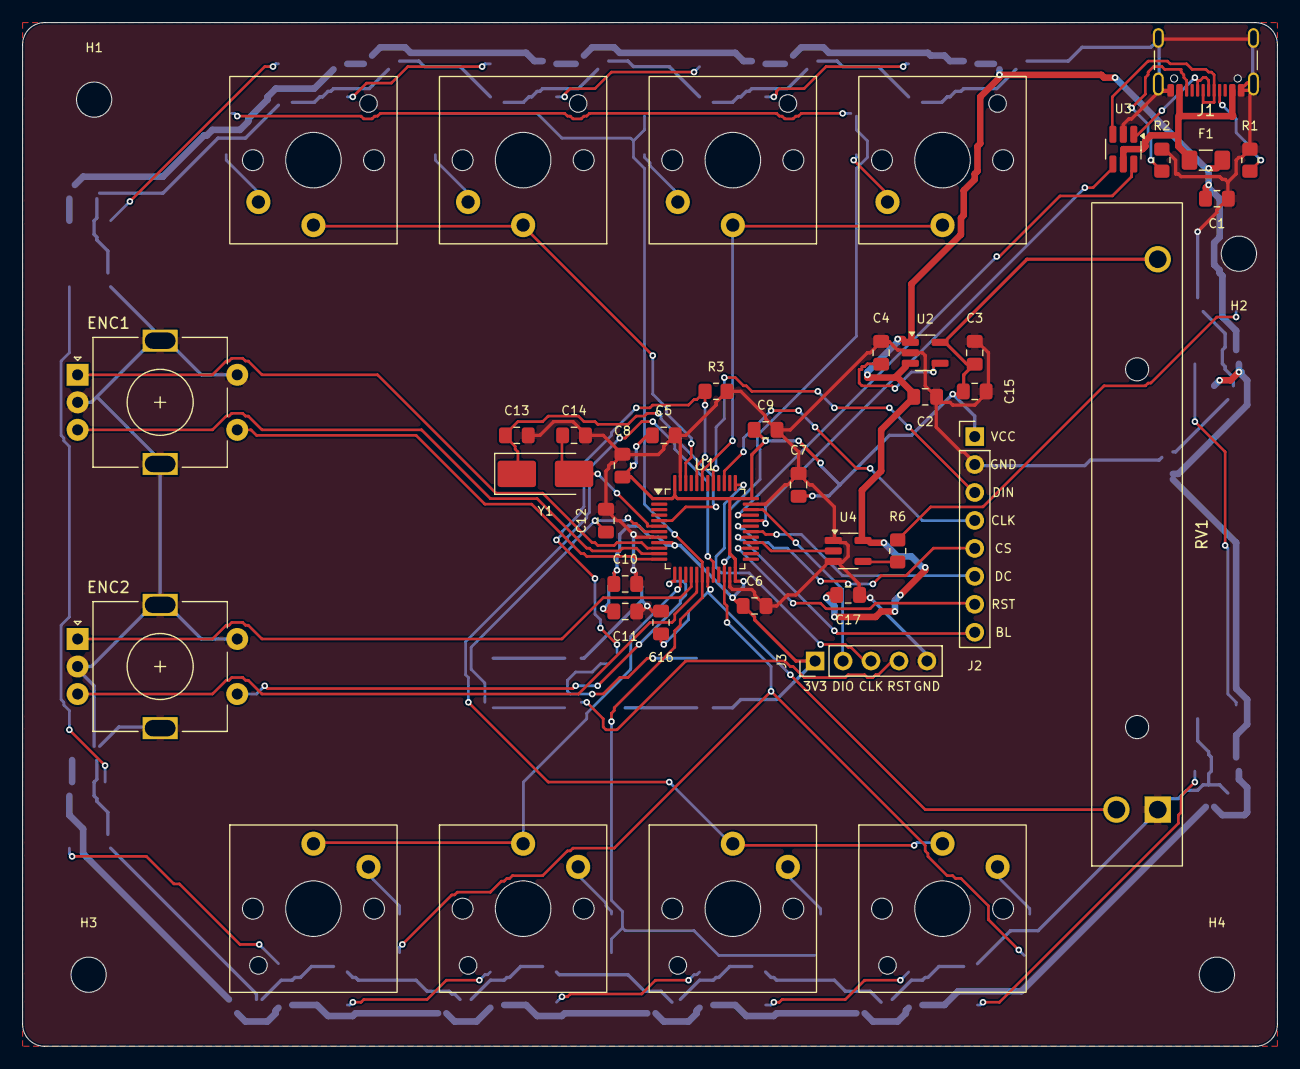
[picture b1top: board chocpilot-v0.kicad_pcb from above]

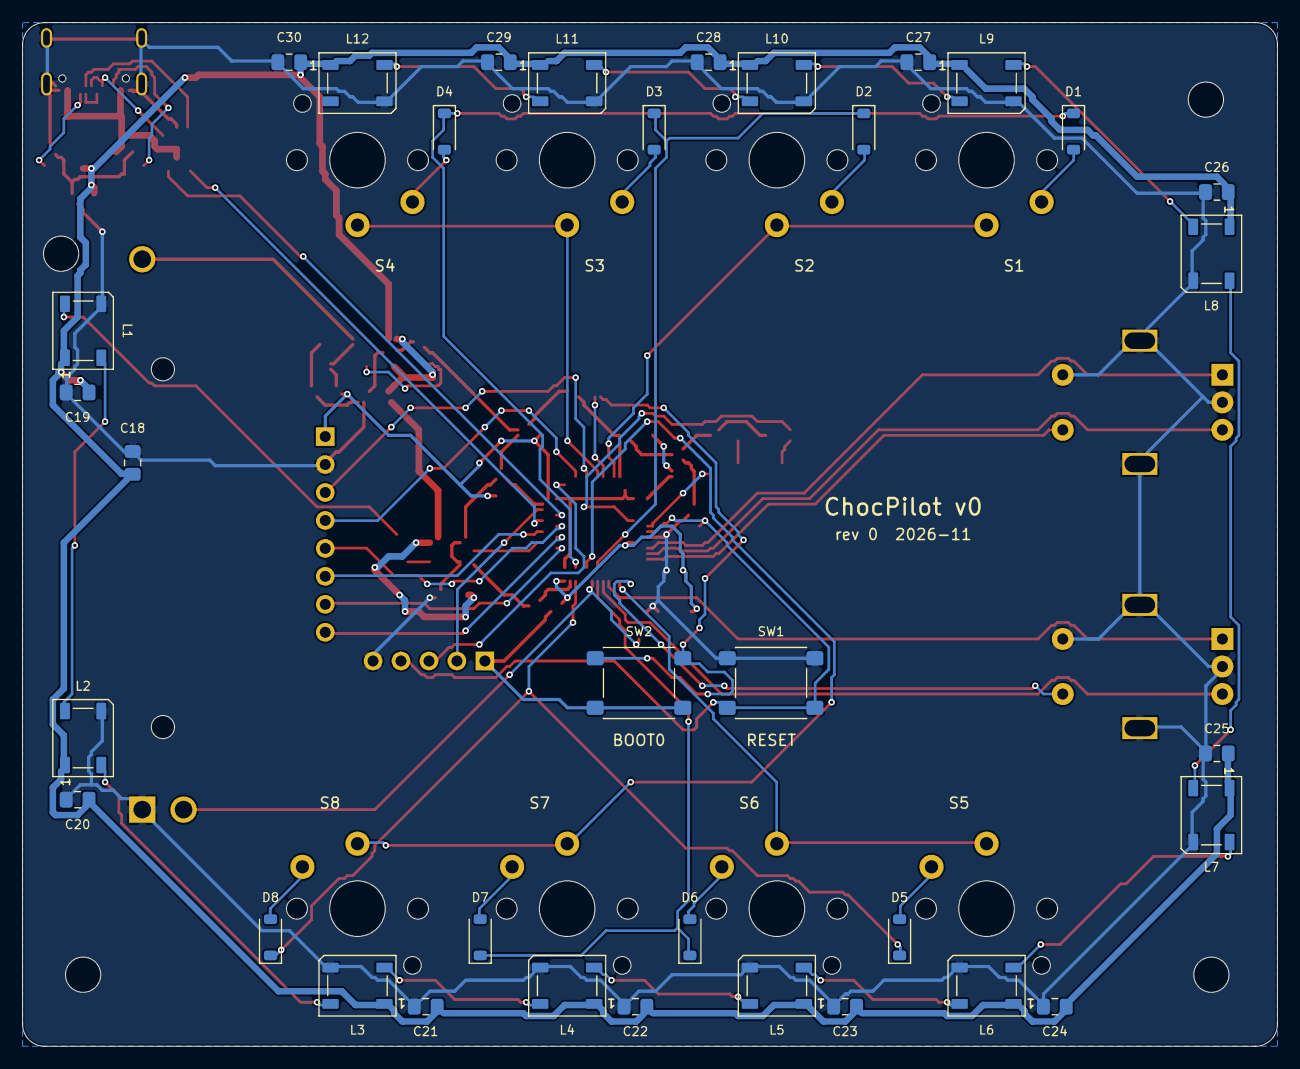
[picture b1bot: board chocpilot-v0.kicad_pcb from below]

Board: 2 copper layers, 114.0 x 93.0 mm, 80 parts (35 on the bottom side), 58 nets.

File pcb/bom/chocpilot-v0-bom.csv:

Poz.,Oznaczenia,Ilość,Opis,Obudowa,Footprint KiCad,Producent,Nr producenta,TME,Amazon (alternatywa),Montaż,Uwagi
1,J1,1,"USB-C 2.0, wlutowane 16 padów SMD (raster 0,5) + 4 kołki THT",SMD 16P + THT,Connector_USB:USB_C_Receptacle_GCT_USB4105-xx-A_16P_TopMnt_Horizontal,GCT,USB4105-GF-A,USB4105-GF-A,,SMD,
2,F1,1,"Bezpiecznik polimerowy PTC 0,5 A (zadziałanie 1 A)",1206,Fuse:Fuse_1206_3216Metric_Pad1.42x1.75mm_HandSolder,Bourns,MF-NSMF050-2,MF-NSMF050-2,,SMD,
3,"R1, R2",2,Rezystor 5.1kΩ 1% 0805,0805,Resistor_SMD:R_0805_2012Metric_Pad1.20x1.40mm_HandSolder,Yageo,RC0805FR-075K1L,RC0805FR-075K1,,SMD,
4,U3,1,Ochrona ESD linii D+/D−,SOT-23-6,Package_TO_SOT_SMD:SOT-23-6_Handsoldering,STMicroelectronics,USBLC6-2SC6,USBLC6-2SC6,,SMD,
5,U2,1,"LDO 3,3 V / 400 mA",SOT-23-5,Package_TO_SOT_SMD:SOT-23-5_HandSoldering,Texas Instruments,TPS73633DBVR,TPS73633DBVR,,SMD,
6,"C1, C3, C15, C18",4,Kondensator 10µF X7R 0805,0805,Capacitor_SMD:C_0805_2012Metric_Pad1.18x1.45mm_HandSolder,KEMET,C0805C106M8RACTU,C0805C106M8RACTU,,SMD,
7,"C2, C11",2,Kondensator 1µF X7R 0805,0805,Capacitor_SMD:C_0805_2012Metric_Pad1.18x1.45mm_HandSolder,KYOCERA AVX,KAM21KR71E105KU,KAM21KR71E105KU,,SMD,
8,C4,1,Kondensator 10nF X7R 0805,0805,Capacitor_SMD:C_0805_2012Metric_Pad1.18x1.45mm_HandSolder,KYOCERA AVX,KGM21NR72A103KT,KGM21NR72A103KT,,SMD,
9,U1,1,"MCU Cortex-M0 48 MHz, USB FS bez kwarcu, bootloader DFU w ROM","LQFP-48 0,5 mm",Package_QFP:LQFP-48_7x7mm_P0.5mm,STMicroelectronics,STM32F072CBT6,STM32F072CBT6,,SMD,
10,"C5–C8, C10, C12, C16, C17, C19–C30",20,Kondensator 100nF X7R 0805,0805,Capacitor_SMD:C_0805_2012Metric_Pad1.18x1.45mm_HandSolder,KYOCERA AVX,KAM21BR71H104KT,KAM21BR71H104KT,,SMD,
11,C9,1,Kondensator 4.7µF X7R 0805,0805,Capacitor_SMD:C_0805_2012Metric_Pad1.18x1.45mm_HandSolder,KYOCERA AVX,KGM21AR71C475KU,KGM21AR71C475KU,,SMD,
12,Y1,1,"Kwarc 8 MHz, CL 18 pF (opcjonalny – USB działa z HSI48+CRS)",5032 2-pad,Crystal:Crystal_SMD_5032-2Pin_5.0x3.2mm_HandSoldering,Abracon,ABM3-8.000MHZ-D2Y-T,ABM3-8.000MHZ-D2Y,,SMD,opcjonalny – USB działa bez kwarcu
13,"C13, C14",2,Kondensator 27pF C0G 0805,0805,Capacitor_SMD:C_0805_2012Metric_Pad1.18x1.45mm_HandSolder,KYOCERA AVX,08055A270GAT2A,08055A270GAT2A,,SMD,
14,R3,1,Rezystor 10kΩ 1% 0805,0805,Resistor_SMD:R_0805_2012Metric_Pad1.20x1.40mm_HandSolder,Yageo,RC0805FR-0710KL,RC0805FR-0710K,,SMD,
15,SW1,1,Reset (od spodu płytki),SMD 6×6 mm,Button_Switch_SMD:SW_SPST_PTS645Sx43SMTR92,C&K,PTS645SM43SMTR92 LFS,PTS645SM43SMTR92,,SMD (spód),
16,SW2,1,BOOT0 – wejście do bootloadera DFU (od spodu płytki),SMD 6×6 mm,Button_Switch_SMD:SW_SPST_PTS645Sx43SMTR92,C&K,PTS645SM43SMTR92 LFS,PTS645SM43SMTR92,,SMD (spód),
17,"ENC1, ENC2",2,Enkoder EC11 z przyciskiem (15 imp./30 zatrzasków),THT,Rotary_Encoder:RotaryEncoder_Alps_EC11E-Switch_Vertical_H20mm,ALPS,EC11E15244G1,EC11E15244G1,,THT,
18,RV1,1,"Potencjometr suwakowy 45 mm, 10 kΩ liniowy (dół = GND, góra = 3,3 V)",THT,chocpilot:Potentiometer_Alps_RS45111_Slide_45mm,ALPS,RS45111A900F,RS45111A900F,,THT,
19,D1–D8,8,Dioda matrycy klawisza K1 (katoda → wiersz),SOD-123,Diode_SMD:D_SOD-123,Vishay,1N4148W-E3-08,1N4148W-E3-08,,SMD (spód),
20,U4,1,"Konwerter poziomu 3,3 V → 5 V dla linii danych LED",SOT-23-5,Package_TO_SOT_SMD:SOT-23-5_HandSoldering,Texas Instruments,SN74AHCT1G125DBVR,SN74AHCT1G125DBVR,,SMD,
21,R6,1,Rezystor 330Ω 1% 0805,0805,Resistor_SMD:R_0805_2012Metric_Pad1.20x1.40mm_HandSolder,Yageo,RC0805FR-07330RL,RC0805FR-07330R,,SMD,
22,L1–L12,12,"LED adresowalny RGB, spód płytki (podświetlenie blatu)",5050 PLCC4,LED_SMD:LED_WS2812B_PLCC4_5.0x5.0mm_P3.2mm,Worldsemi,WS2812B-V6,WS2812B-V6,WS2812B 5050 SMD chip (np. BTF-LIGHTING),SMD (spód),
23,S1–S8,8,"Przełącznik Kailh Choc V1 (low profile, trzpień z dwiema nogami)",THT,,Kailh,CPG1350 (Choc V1),brak w TME,Kailh Choc V1 (np. Red / Brown),THT (lutowany od spodu),brak w TME; footprint przyjmuje też Choc V2 (wtedy keycapy MX)
24,—,8,Keycap Choc V1 1u – drukowany (case/chocpilot_keycap.stl),—,,—,—,—,—,druk 3D,równo z górą obudowy; opis w case/README.md
25,"ENC1, ENC2",2,Gałka enkodera Ø18 – drukowana (case/chocpilot_knob.stl),—,,—,—,—,—,druk 3D,oś D 6 mm
26,RV1,1,Nakładka suwaka – drukowana (case/chocpilot_slider_cap.stl),—,,—,—,—,—,druk 3D,"dźwignia 4 × 1,2 mm"
27,J2,1,"Ekran LCD 2"" IPS 240×320, ST7789V, SPI (Waveshare 2inch LCD Module, z kablem PH2.0)",58 × 35 mm,,Waveshare,17344,WSH-17344,,"w obudowie, kabel PH2.0 → J2","kabel 1:1 na J2 (VCC na pin 1); zasilanie 3,3 V – logika modułu = VCC"
28,H1–H4,4,Wkręt M3 × 14 z łbem stożkowym (ISO 10642) – płytka i obudowa,—,,—,—,—,M3 countersunk screws,—,od spodu przez dno w kołki obudowy
29,—,4,Wkręt M2 × 5 – mocowanie ekranu w obudowie,—,,—,—,—,M2 screws assortment,—,"w tuleje obudowy (otwór Ø1,6)"

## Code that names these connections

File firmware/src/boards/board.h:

// Mapa pinów ChocPilot: własna płytka ze STM32F072CBT6 (pcb, docs/PINOUT.md).
// Numery pinów rdzenia STM32duino (PA0…PC15); w komentarzu nóżka LQFP-48 i sieć ze schematu.
#pragma once

#include <Arduino.h>
#include <stdint.h>

#include "device_config.h"

namespace chocpilot {
namespace board {

constexpr const char* kBoardId = "chocpilot";
constexpr const char* kBoardName = "ChocPilot";
constexpr bool kHasEncoders = true;

// Matryca 2×4 COL2ROW (dioda przy każdym klawiszu): wiersz = wyjście LOW, kolumna = wejście
// z pull-upem. Kolumna = para sąsiednich klawiszy w jednym rzędzie, wiersz 0 = klawisze
// wewnętrzne, wiersz 1 = zewnętrzne (krótsze ścieżki na płytce).
constexpr uint8_t kRowPins[kRows] = {
    PB0,   // ROW0 – nóżka 18: K2, K3, K6, K7
    PB11,  // ROW1 – nóżka 22: K1, K4, K5, K8
};
constexpr uint8_t kColPins[kCols] = {
    PB9,  // COL0 – nóżka 46: K1/K2
    PB7,  // COL1 – nóżka 43: K3/K4
    PA4,  // COL2 – nóżka 14: K5/K6
    PB2,  // COL3 – nóżka 20: K7/K8
};
// Numer klawisza Kn w punkcie matrycy (wiersz, kolumna) – pcb/…/tools/design.py: MATRIX_KEYS.
constexpr uint8_t kKeyMap[kRows][kCols] = {{2, 3, 6, 7}, {1, 4, 5, 8}};

// Ekran LCD 2" ST7789V 240×320 (Waveshare WSH-17344) na SPI1, złącze J2.
constexpr uint8_t kLcdSck = PB3;   // nóżka 39, SPI1_SCK (AF0)
constexpr uint8_t kLcdMosi = PB5;  // nóżka 41, SPI1_MOSI (AF0)
constexpr uint8_t kLcdCs = PA10;   // nóżka 31
constexpr uint8_t kLcdDc = PA9;    // nóżka 30
constexpr uint8_t kLcdRst = PB14;  // nóżka 27
constexpr uint8_t kLcdBl = PA8;    // nóżka 29, TIM1_CH1 – PWM podświetlenia

// Pokrętła EC11 (15 impulsów / 30 zatrzasków): A/B na wejściach timerów w trybie enkodera.
constexpr uint8_t kEnc1A = PA0;   // nóżka 10, TIM2_CH1 (AF2)
constexpr uint8_t kEnc1B = PA1;   // nóżka 11, TIM2_CH2 (AF2)
constexpr uint8_t kEnc1Sw = PA2;  // nóżka 12
constexpr uint8_t kEnc2A = PA6;   // nóżka 16, TIM3_CH1 (AF1)
constexpr uint8_t kEnc2B = PA7;   // nóżka 17, TIM3_CH2 (AF1)
constexpr uint8_t kEnc2Sw = PA3;  // nóżka 13
// Kierunek liczenia: +1 = obrót w prawo daje dodatnią deltę. Zmień na −1, jeśli jest odwrotnie.
constexpr int8_t kEncoderDir = 1;
// Zliczenia timera (tryb x4) na jeden zatrzask EC11E15244G1: 15 impulsów × 4 / 30 zatrzasków.
constexpr uint8_t kEncoderCountsPerDetent = 2;

// Suwak ALPS RS45111 10 kΩ: dzielnik 3,3 V → ADC (pin 1 = GND na dole, pin 3 = 3,3 V u góry).
constexpr uint8_t kSlider = PB1;  // nóżka 19, ADC_IN9

// 12 × WS2812B-V6 na spodzie: dane PB15 (SPI2_MOSI, AF0) → 74AHCT1G125 → L1 … L12.
constexpr uint8_t kLedData = PB15;  // nóżka 28
constexpr uint8_t kLedCount = 12;
// Dioda przy klawiszu (błysk po naciśnięciu): łańcuch L1 … L12 = indeksy 0 … 11. Górny rząd
// K1–K4 nad diodami L9–L12, dolny K5–K8 pod L6, L5, L4, L3 (pcb/…/tools/design.py: LED).
constexpr uint8_t kKeyLed[kRows * kCols] = {8, 9, 10, 11, 5, 4, 3, 2};

}  // namespace board
}  // namespace chocpilot
